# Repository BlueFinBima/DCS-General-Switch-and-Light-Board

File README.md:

# DCS General Switch and Light Board
This is a general i2c board for switches and LEDs.  It uses the Holtek HT16K33 chip and the intent is to use this board with the ESP32 controller from the F/A-18C UFC project.

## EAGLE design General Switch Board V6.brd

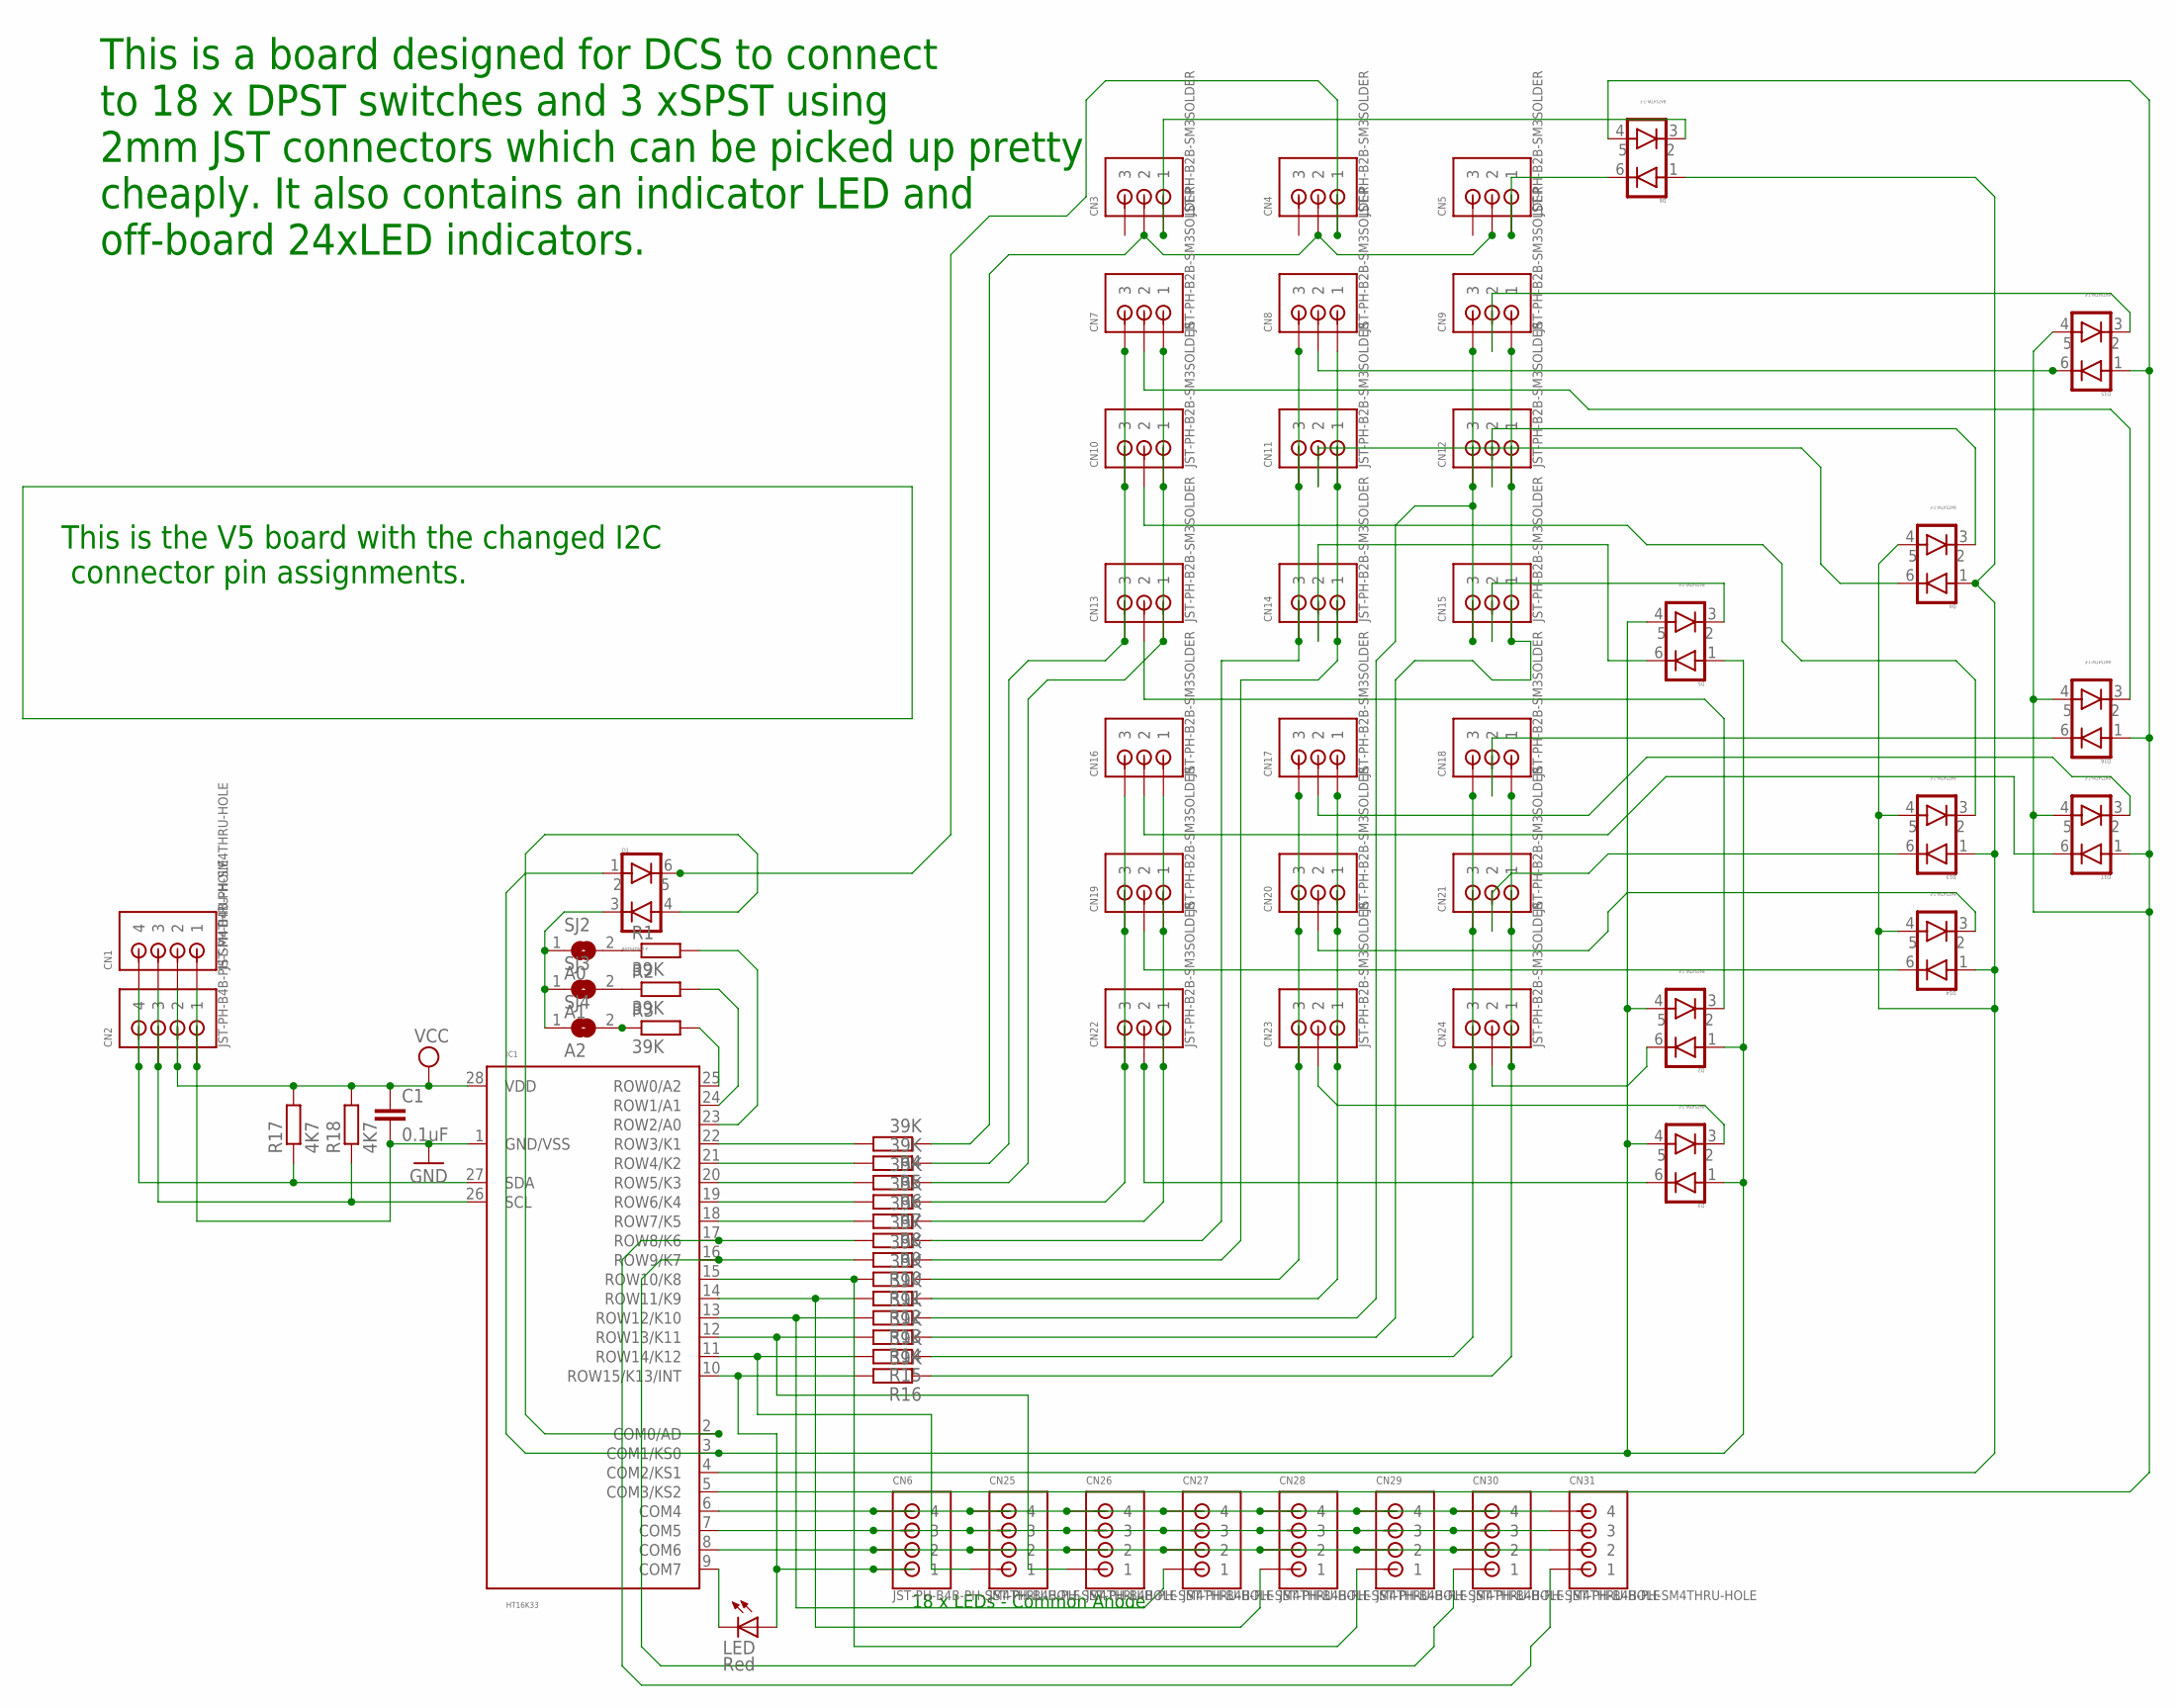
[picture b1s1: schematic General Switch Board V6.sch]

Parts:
C1: 0.1uF; C0805
CN1, CN2, CN6, CN25, CN26, CN27, CN28, CN29, CN30, CN31: JST-PH-B4B-PH-SM4THRU-HOLE; B4B-PH-SOLDER
CN3, CN4, CN5, CN7, CN8, CN9, CN10, CN11, CN12, CN13, CN14, CN15, CN16, CN17, CN18, CN19, CN20, CN21, CN22, CN23, CN24: JST-PH-B2B-SM3SOLDER; B3B-PH-SOLDER
D1, D2, D3, D4, D5, D6, D13, D14, D15, D16, D17: BAT54TW-7-F; SSOT6
IC1: HT16K33; SOIC28
LED: Red; CHIPLED_1206
R1, R2, R3, R4, R5, R6, R7, R8, R9, R10, R11, R12, R13, R14, R15, R16: 39K; R0805
R17, R18: 4K7; R0805
SJ2: A0; SJ
SJ3: A1; SJ
SJ4: A2; SJ

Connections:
GND: C1.2, CN1.P1 (1), CN2.P1 (1), IC1.1 (GND/VSS)
unnamed: IC1.22 (ROW3/K1), R4.2
unnamed: CN19.P2 (2), D14.6 (C1)
unnamed: CN3.P2 (2), CN4.P2 (2), CN5.P2 (2), R4.1
unnamed: D1.4 (A2), IC1.2 (COM0/AD)
unnamed: CN25.P1 (1), IC1.11 (ROW14/K12), R15.2
unnamed: IC1.9 (COM7), LED.C
unnamed: IC1.21 (ROW4/K2), R5.2
unnamed: IC1.20 (ROW5/K3), R6.2
unnamed: CN3.P1 (1), D6.3 (C2)
unnamed: IC1.19 (ROW6/K4), R7.2
unnamed: CN5.P1 (1), D6.6 (C1)
unnamed: CN4.P1 (1), D1.6 (C1)
unnamed: CN17.P2 (2), D17.3 (C2)
unnamed: CN9.P1 (1), CN12.P1 (1), CN15.P1 (1), R14.1
unnamed: CN1.P3 (3), CN2.P3 (3), IC1.26 (SCL), R18.1
unnamed: CN24.P2 (2), D2.6 (C1)
unnamed: CN6.P2 (2), CN25.P2 (2), CN26.P2 (2), CN27.P2 (2), CN28.P2 (2), CN29.P2 (2), CN30.P2 (2), CN31.P2 (2), IC1.8 (COM6)
unnamed: CN8.P2 (2), D15.6 (C1)
unnamed: D6.4 (A2), D15.1 (A1), D15.4 (A2), D16.1 (A1), D16.4 (A2), D17.1 (A1), D17.4 (A2), IC1.5 (COM3/KS2)
unnamed: IC1.18 (ROW7/K5), R8.2
unnamed: CN20.P2 (2), D14.3 (C2)
unnamed: IC1.24 (ROW1/A1), R2.2
unnamed: CN15.P2 (2), D5.3 (C2)
unnamed: IC1.23 (ROW2/A0), R1.2
unnamed: CN14.P2 (2), D5.6 (C1)
unnamed: IC1.25 (ROW0/A2), R3.2
unnamed: CN13.P2 (2), D2.3 (C2)
unnamed: CN6.P3 (3), CN25.P3 (3), CN26.P3 (3), CN27.P3 (3), CN28.P3 (3), CN29.P3 (3), CN30.P3 (3), CN31.P3 (3), IC1.7 (COM5)
unnamed: CN21.P2 (2), D13.6 (C1)
unnamed: CN16.P2 (2), D17.6 (C1)
unnamed: CN18.P2 (2), D16.6 (C1)
unnamed: CN10.P2 (2), D13.3 (C2)
unnamed: CN11.P2 (2), D4.6 (C1)
unnamed: CN12.P2 (2), D4.3 (C2)
unnamed: CN22.P2 (2), D3.6 (C1)
unnamed: CN9.P2 (2), D15.3 (C2)
unnamed: CN6.P4 (4), CN25.P4 (4), CN26.P4 (4), CN27.P4 (4), CN28.P4 (4), CN29.P4 (4), CN30.P4 (4), CN31.P4 (4), IC1.6 (COM4)
unnamed: CN18.P3 (3), CN21.P3 (3), CN24.P3 (3), R15.1
unnamed: CN7.P2 (2), D16.3 (C2)
unnamed: CN23.P2 (2), D3.3 (C2)
unnamed: CN27.P1 (1), IC1.13 (ROW12/K10), R13.2
unnamed: D1.1 (A1), D2.1 (A1), D2.4 (A2), D3.1 (A1), D3.4 (A2), D5.1 (A1), D5.4 (A2), IC1.3 (COM1/KS0)
unnamed: CN9.P3 (3), CN12.P3 (3), CN15.P3 (3), R13.1
unnamed: CN26.P1 (1), IC1.12 (ROW13/K11), R14.2
unnamed: CN30.P1 (1), IC1.16 (ROW9/K7), R10.2
unnamed: CN28.P1 (1), IC1.14 (ROW11/K9), R12.2
unnamed: CN29.P1 (1), IC1.15 (ROW10/K8), R11.2
unnamed: CN18.P1 (1), CN21.P1 (1), CN24.P1 (1), R16.1
unnamed: CN31.P1 (1), IC1.17 (ROW8/K6), R9.2
unnamed: D4.1 (A1), D4.4 (A2), D6.1 (A1), D13.1 (A1), D13.4 (A2), D14.1 (A1), D14.4 (A2), IC1.4 (COM2/KS1)
unnamed: CN6.P1 (1), IC1.10 (ROW15/K13/INT), LED.A, R16.2
unnamed: CN7.P1 (1), CN10.P1 (1), CN13.P1 (1), R6.1
unnamed: R3.1, SJ4.2
unnamed: D1.3 (C2), SJ2.1, SJ3.1, SJ4.1
unnamed: R1.1, SJ2.2
unnamed: R2.1, SJ3.2
unnamed: CN16.P1 (1), CN19.P1 (1), CN22.P1 (1), R8.1
unnamed: CN7.P3 (3), CN10.P3 (3), CN13.P3 (3), R5.1
unnamed: CN16.P3 (3), CN19.P3 (3), CN22.P3 (3), R7.1
unnamed: CN17.P3 (3), CN20.P3 (3), CN23.P3 (3), R11.1
unnamed: CN17.P1 (1), CN20.P1 (1), CN23.P1 (1), R12.1
unnamed: CN8.P1 (1), CN11.P1 (1), CN14.P1 (1), R10.1
unnamed: CN8.P3 (3), CN11.P3 (3), CN14.P3 (3), R9.1
SDA: CN1.P4 (4), CN2.P4 (4), IC1.27 (SDA), R17.1
VCC: C1.1, CN1.P2 (2), CN2.P2 (2), IC1.28 (VDD), R17.2, R18.2

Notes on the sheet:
This is a board designed for DCS to connect to 18 x DPST switches and 3 xSPST using 2mm JST connectors which can be picked up pretty cheaply. It also contains an indicator LED and off-board 24xLED indicators.
18 x LEDs - Common Anode
This is the V5 board with the changed I2C connector pin assignments.

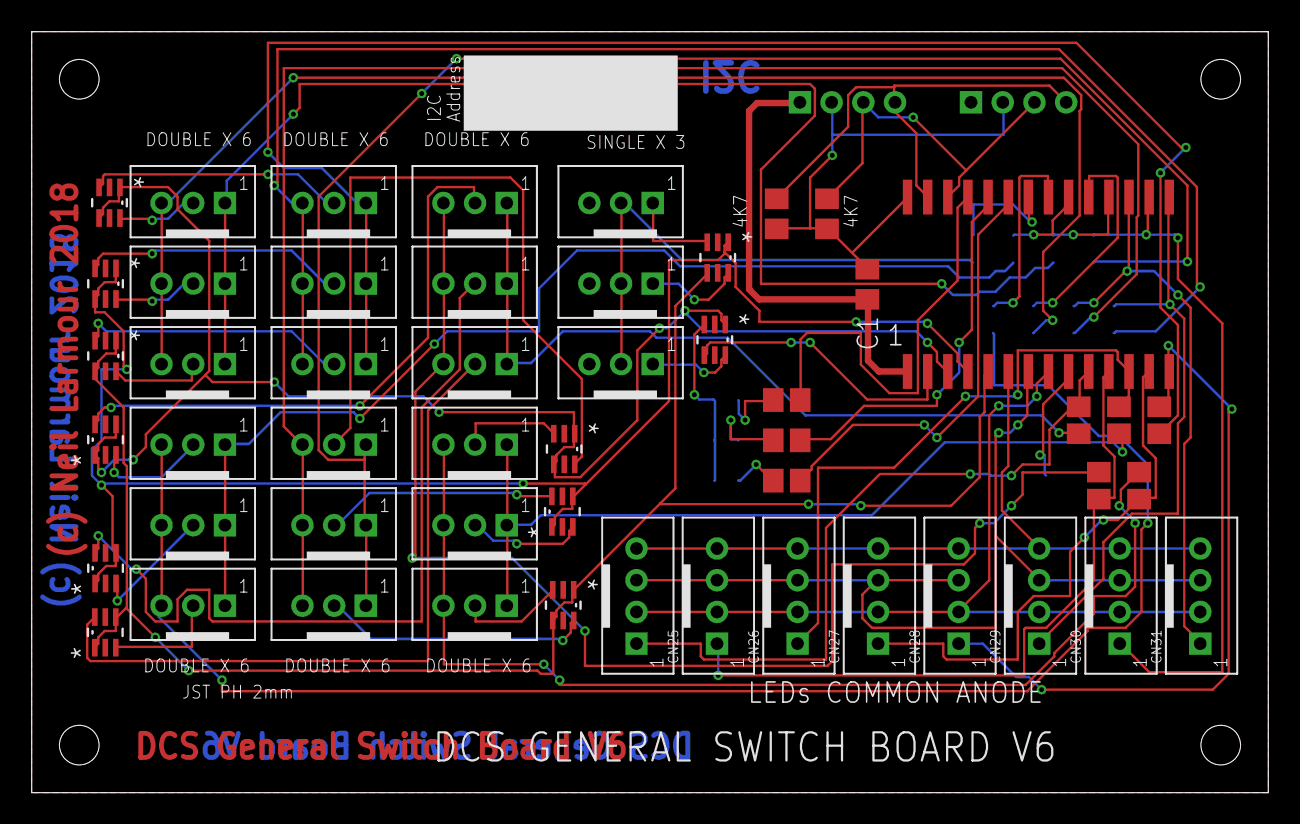
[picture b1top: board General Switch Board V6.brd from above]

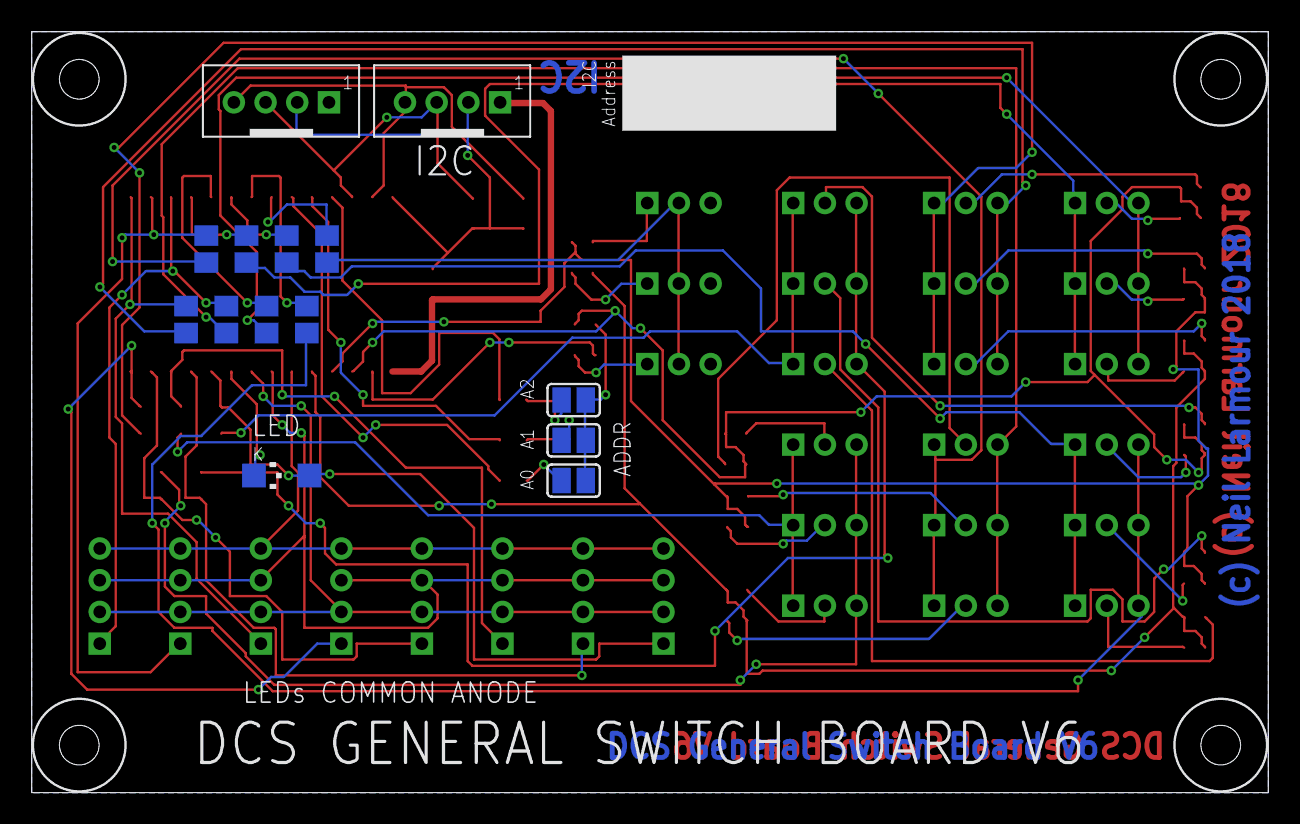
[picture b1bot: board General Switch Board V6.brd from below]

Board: 2 copper layers, 78.0 x 48.0 mm, 70 parts (18 on the bottom side), 66 nets.

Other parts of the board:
U$2, U$3, U$4, U$6: DRIL-2,5
